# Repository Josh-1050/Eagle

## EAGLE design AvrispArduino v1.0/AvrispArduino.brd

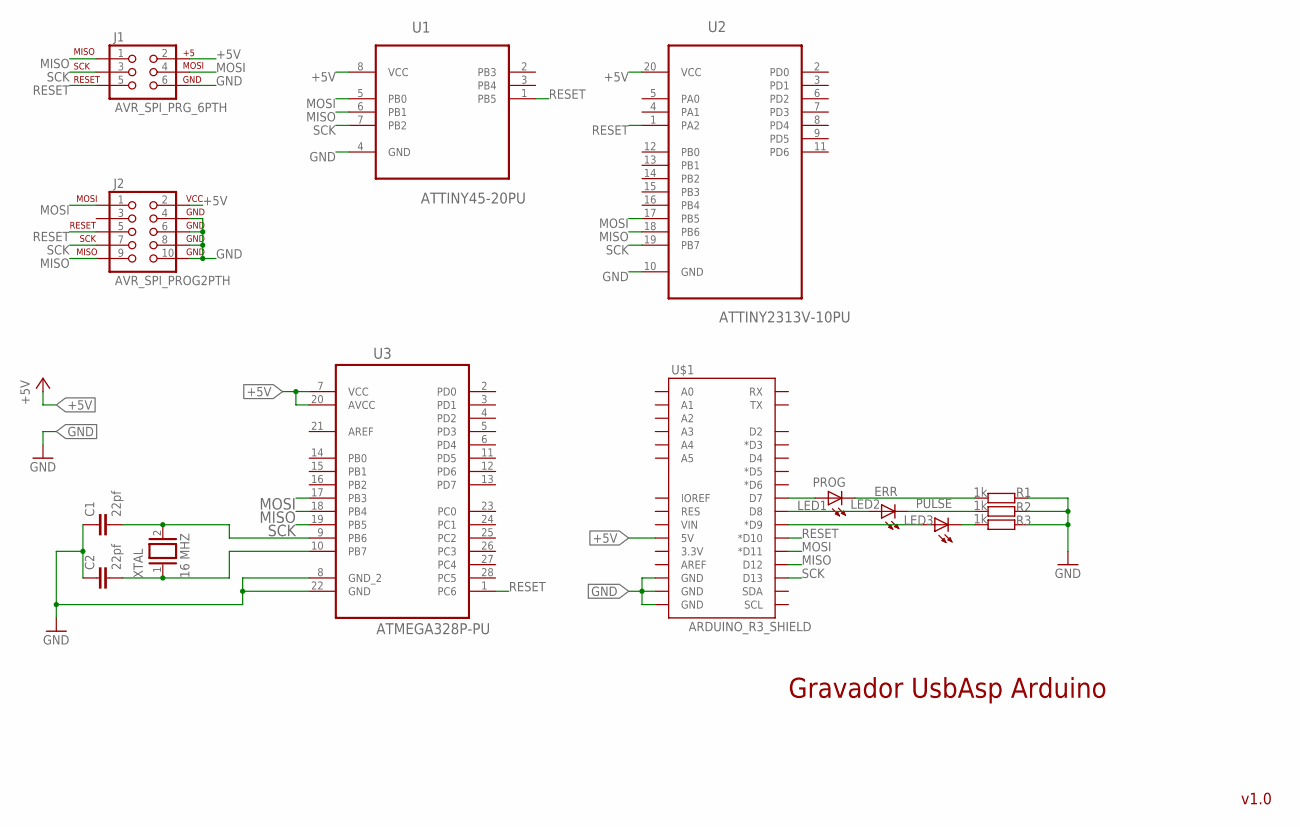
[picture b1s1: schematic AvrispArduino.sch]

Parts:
C1, C2: 22pf; C025-025X050
J1: AVR_SPI_PRG_6PTH; 2X3
J2: AVR_SPI_PROG2PTH; AVR_ICSP
LED1: PROG; LED3MM
LED2: ERR; LED3MM
LED3: PULSE; LED3MM
R1, R2, R3: 1k; 0207/10
U1: ATTINY45-20PU; DIP254P762X533-8
U2: ATTINY2313V-10PU; DIP254P762X533-20
U3: ATMEGA328P-PU; DIP254P762X457-28
U$1: ARDUINO_R3_SHIELD; UNO_R3_SHIELD
XTAL: 16 MHZ; QS

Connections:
+5V: J1.2, J2.2 (VCC), U1.8 (VCC), U2.20 (VCC), U3.7 (VCC), U3.20 (AVCC), U$1.5V
GND: C1.1, C2.1, J1.6, J2.4 (GND), J2.6 (GND), J2.8 (GND), J2.10 (GND), R1.2, R2.2, R3.2, U1.4 (GND), U2.10 (GND), U3.8 (GND_2), U3.22 (GND), U$1.GND@0 (GND), U$1.GND@1 (GND), U$1.GND@2 (GND)
MISO: J1.1, J2.9 (MISO), U1.6 (PB1), U2.18 (PB6), U3.18 (PB4), U$1.D12
MOSI: J1.4, J2.1 (MOSI), U1.5 (PB0), U2.17 (PB5), U3.17 (PB3), U$1.D11 (*D11)
unnamed: LED1.A, U$1.D7
unnamed: LED2.A, U$1.D8
unnamed: LED3.A, U$1.D9 (*D9)
unnamed: LED1.K (C), R1.1
unnamed: LED2.K (C), R2.1
unnamed: LED3.K (C), R3.1
unnamed: C1.2, U3.9 (PB6), XTAL.2
unnamed: C2.2, U3.10 (PB7), XTAL.1
RESET: J1.5, J2.5 (RESET), U1.1 (PB5), U2.1 (PA2), U3.1 (PC6), U$1.D10 (*D10)
SCK: J1.3, J2.7 (SCK), U1.7 (PB2), U2.19 (PB7), U3.19 (PB5), U$1.D13

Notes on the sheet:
Gravador UsbAsp Arduino
v1.0

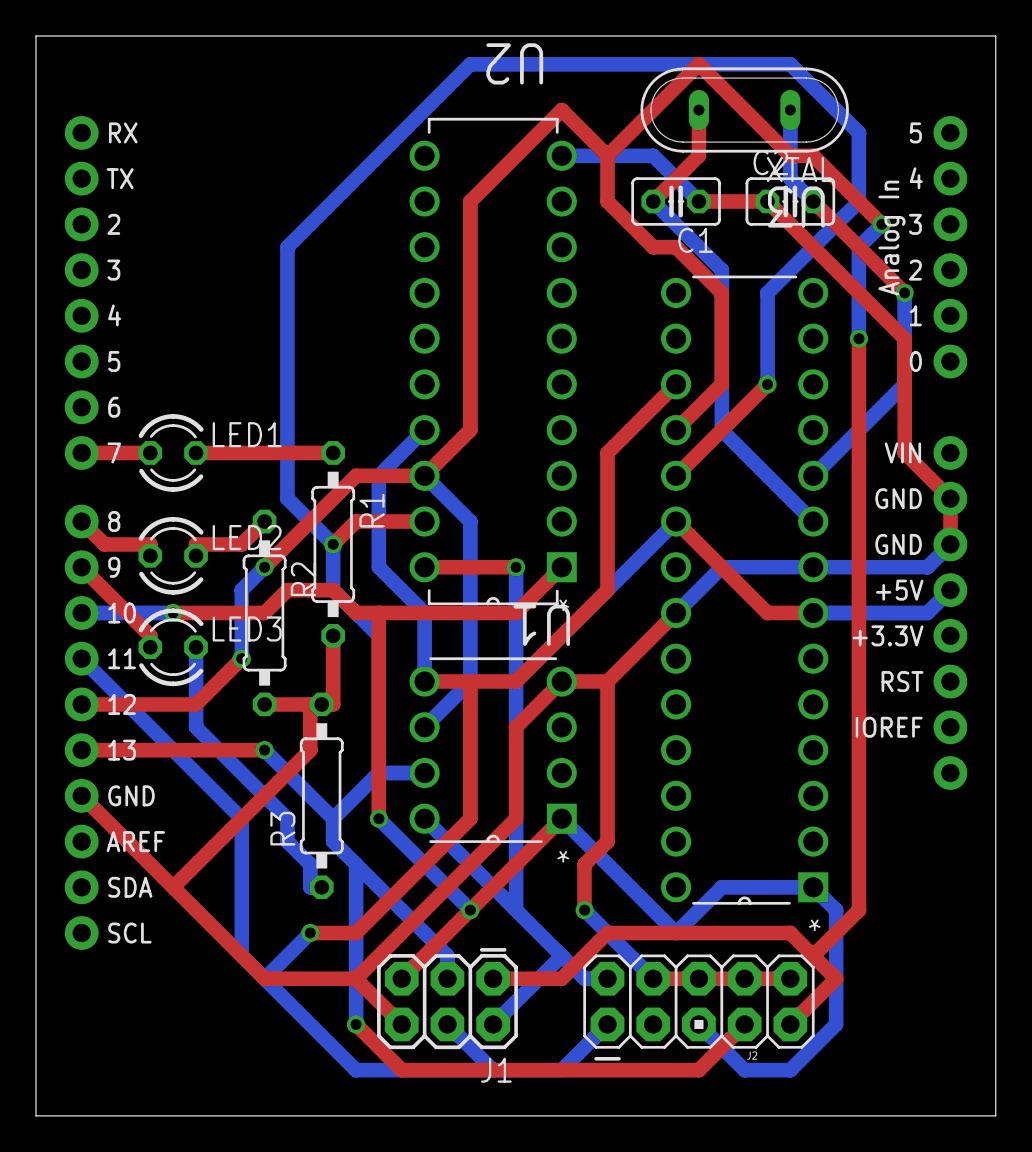
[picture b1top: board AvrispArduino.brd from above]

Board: 2 copper layers, 53.3 x 60.0 mm, 15 parts (0 on the bottom side), 14 nets.

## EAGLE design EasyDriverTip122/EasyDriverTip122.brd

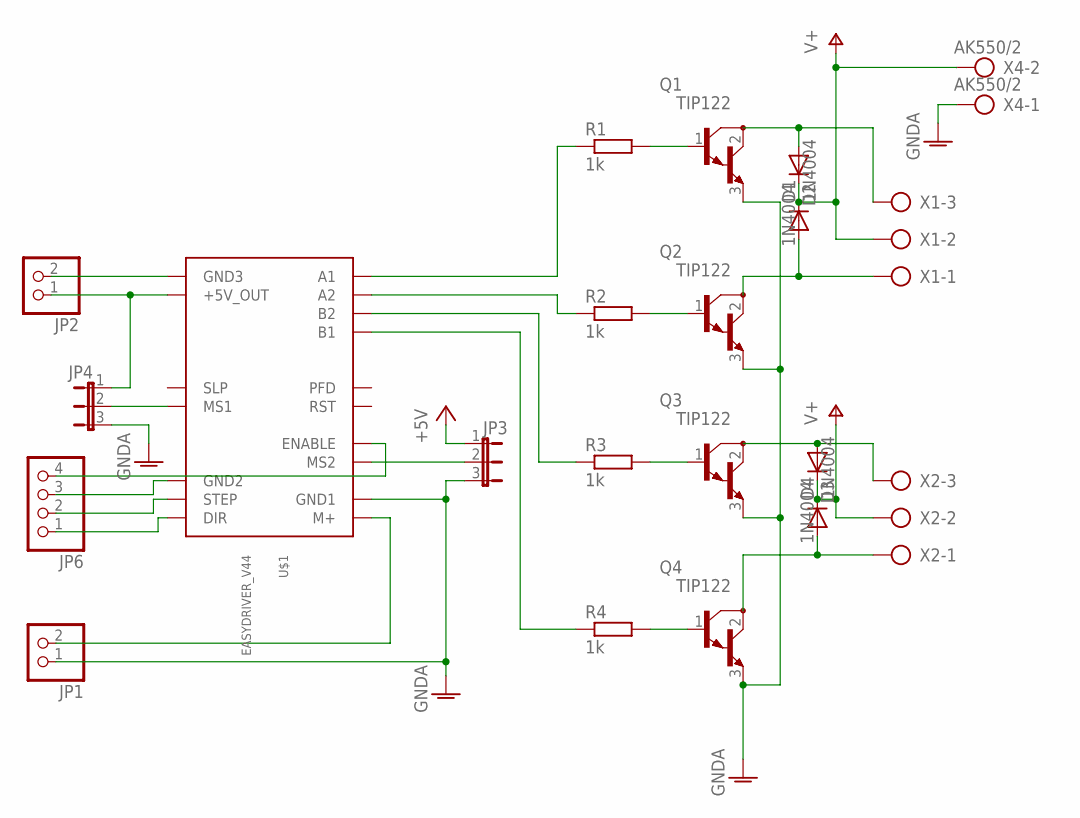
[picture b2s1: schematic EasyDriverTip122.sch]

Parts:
D1, D2, D3, D4: 1N4004; DO41-10
JP1, JP2: PINHD-1X2; 1X02
JP3, JP4: JP2E; JP2
JP6: PINHD-1X4; 1X04
Q1, Q2, Q3, Q4: TIP122; TO220V
R1, R2, R3, R4: 1k; 0204/7
U$1: EASYDRIVER_V44
X1, X2: AK500/3
X4: AK550/2

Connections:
+5V: JP2.1, JP3.1, JP4.1, U$1.P$11 (+5V_OUT)
GNDA: JP1.1, JP3.3, JP4.3, Q1.3 (E), Q2.3 (E), Q3.3 (E), Q4.3 (E), U$1.GND1, X4.1
unnamed: JP4.2, U$1.MS1
unnamed: JP3.2, U$1.MS2
unnamed: JP6.3, U$1.GND2
unnamed: JP6.2, U$1.STEP
unnamed: JP6.4, U$1.ENABLE
unnamed: JP1.2, U$1.M+
unnamed: JP2.2, U$1.GND3
unnamed: JP6.1, U$1.DIR
unnamed: Q1.1 (B), R1.2
unnamed: Q2.1 (B), R2.2
unnamed: Q3.1 (B), R3.2
unnamed: Q4.1 (B), R4.2
unnamed: R1.1, U$1.A1
unnamed: R2.1, U$1.A2
unnamed: R3.1, U$1.B2
unnamed: R4.1, U$1.B1
unnamed: D2.A, Q1.2 (C), X1.3
unnamed: D1.A, Q2.2 (C), X1.1
unnamed: D3.A, Q3.2 (C), X2.3
unnamed: D4.A, Q4.2 (C), X2.1
V+: D1.C, D2.C, D3.C, D4.C, X1.2, X2.2, X4.2

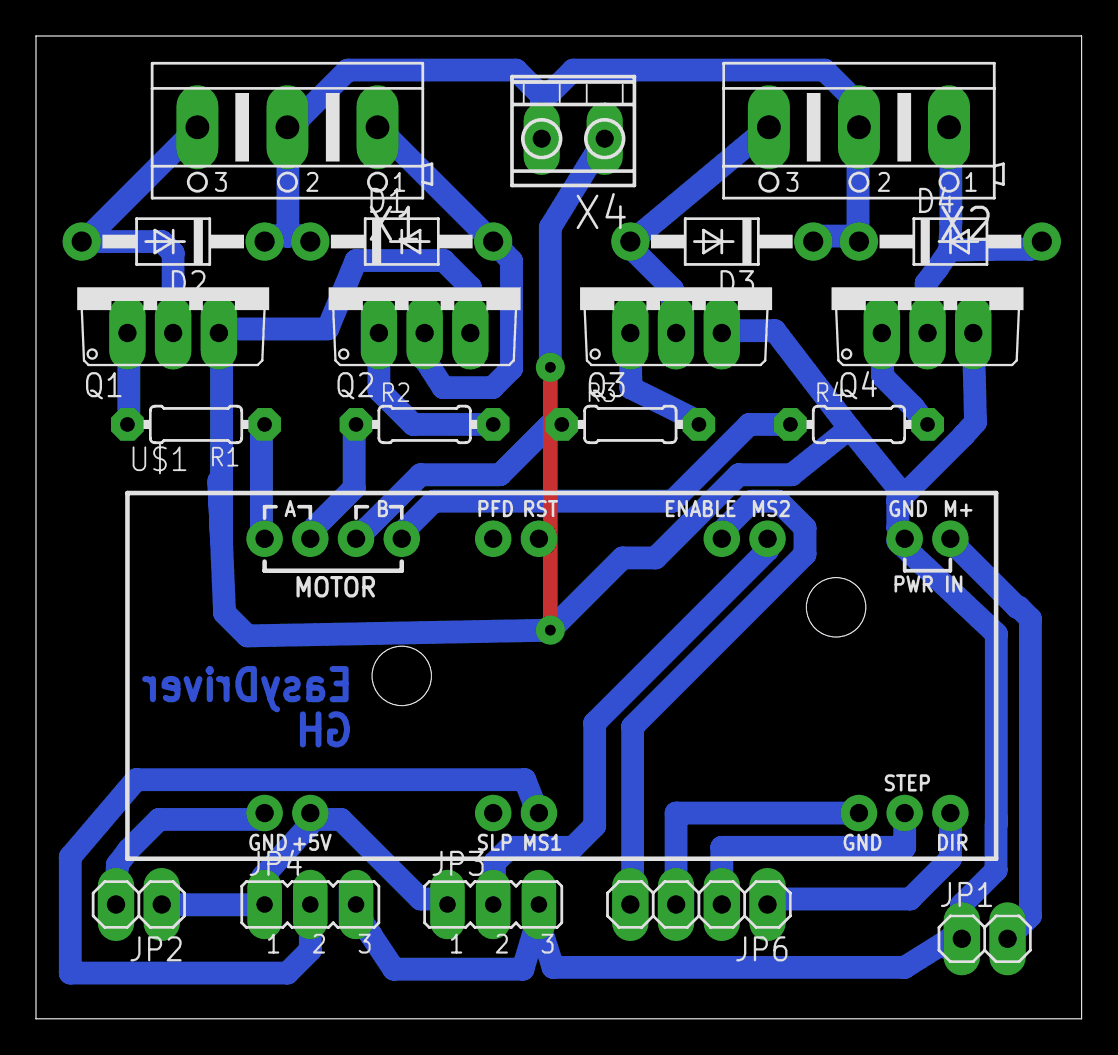
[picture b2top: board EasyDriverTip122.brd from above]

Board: 2 copper layers, 58.1 x 54.6 mm, 21 parts (0 on the bottom side), 23 nets.

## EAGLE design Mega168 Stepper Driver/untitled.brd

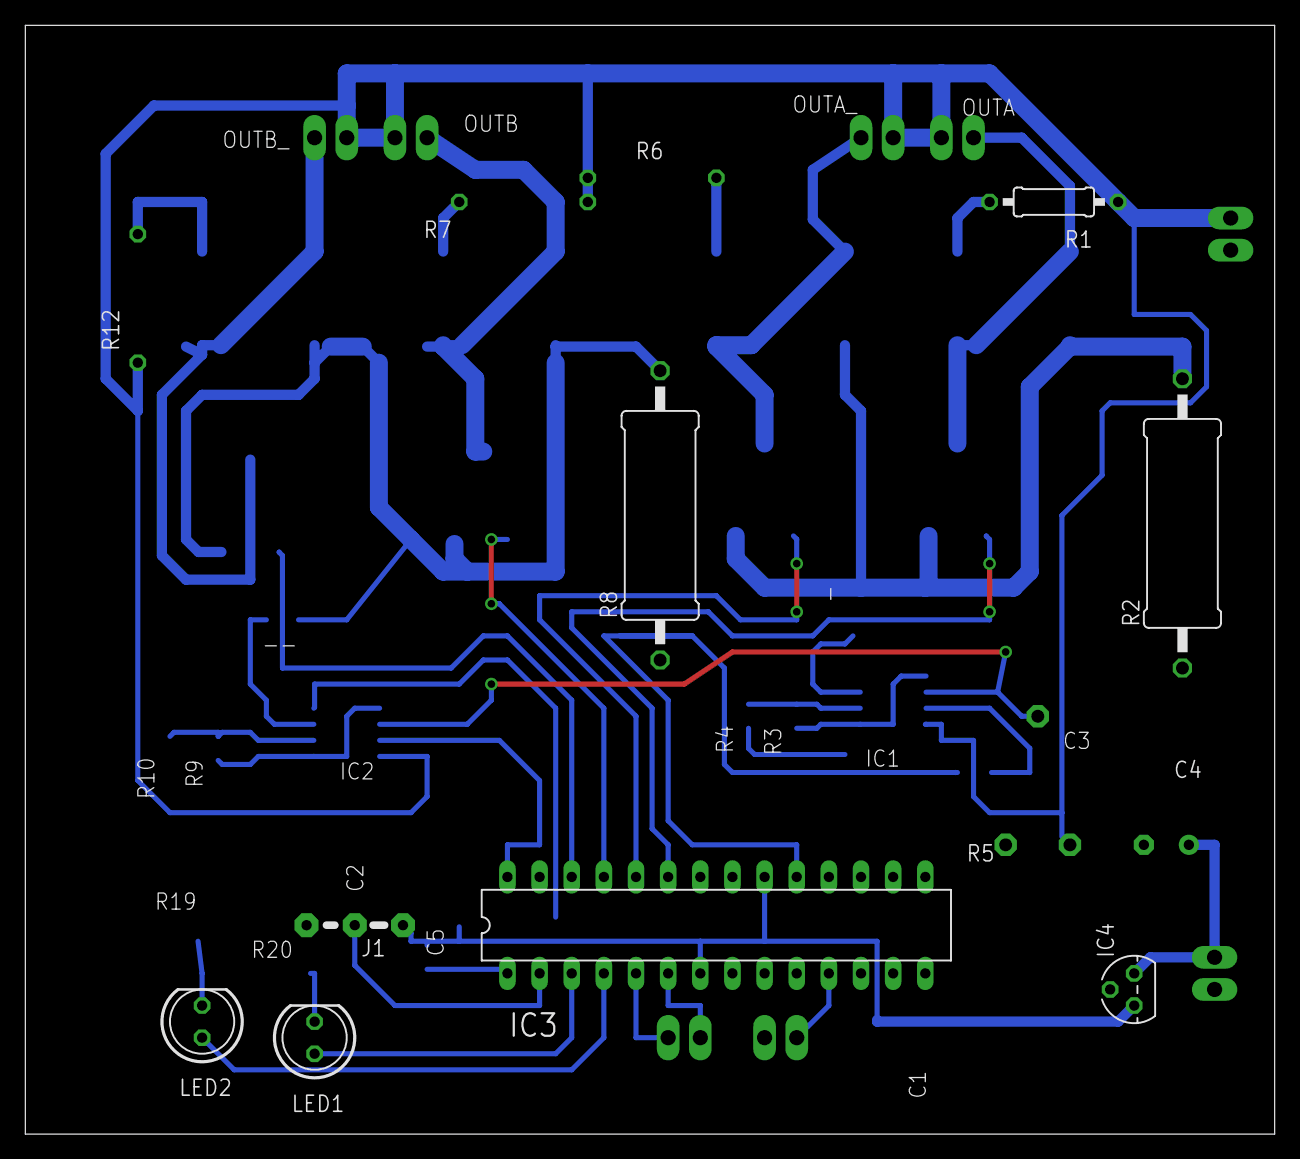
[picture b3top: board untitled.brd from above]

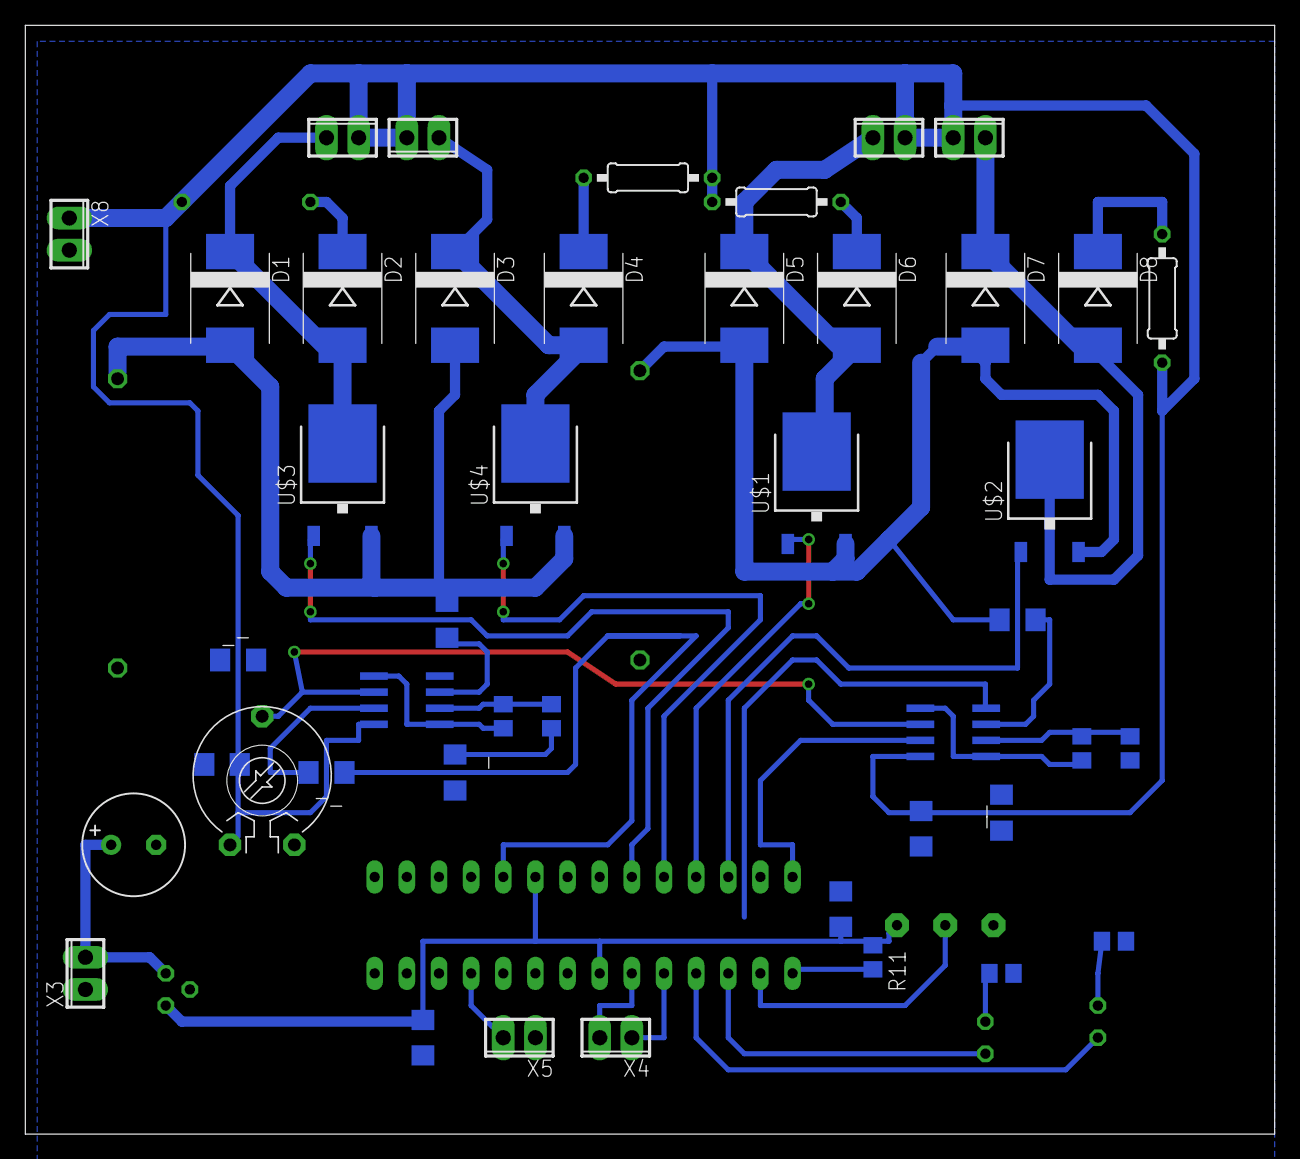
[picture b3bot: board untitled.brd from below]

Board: 2 copper layers, 98.7 x 87.6 mm, 52 parts (44 on the bottom side), 35 nets.

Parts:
-: R1206
--: R1206
-_: R1206
C1, C2, C3, C5: 0.1u; C1206
C4: 10u; E3,5-8
D1, D2, D3, D4, D5, D6, D7, D8: S3D; SMC
IC1, IC2: LM358D; SO08
IC3: MEGA48/88/168-PU; DIL28-3
IC4: 7805L; TO92
J1: 04C
LED1, LED2: LED5MM
OUTA: 2POL254
OUTA_: 2POL254
OUTB: 2POL254
OUTB_: 2POL254
R1, R6, R7, R12: 1k; 0207/10
R2, R8: 0.1; 0617/22
R3, R9, R11: 10k; R0805
R4, R10: 2.2k; R0805
R5: PT-10
R19, R20: 1K; R0805
U$1, U$2, U$3, U$4: NTD3055L104G; TO252
X3, X4, X5, X8: 2POL254
_: R1206
_-: R1206
__: R1206

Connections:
CTRLA: IC3.23, U$3.1
CTRLA_: IC3.24, U$4.1
CTRLB: IC3.25, U$1.1
CTRLB_: IC3.26, U$2.1
GND: C1.2, C2.1, C3.1, C4.-, C5.2, IC1.4, IC2.4, IC3.8, IC3.21, IC3.22, IC4.2, J1.3, R2.1, R4.2, R5.2, R8.1, R10.2, R19.2, R20.2, X3.1, X5.1, X8.2, _.1, _.2, _-.1, _-.2, __.1, __.2
unnamed: IC1.1, IC1.5, R3.1
unnamed: IC1.2, R3.2, R4.1
unnamed: -_.1, IC3.19
unnamed: IC2.7, IC3.28
unnamed: IC3.11, X5.2
unnamed: IC1.6, IC2.6, R5.3
unnamed: D1.C, D2.A, OUTA.1, U$3.3
unnamed: D2.C, R1.1
unnamed: C4.+, IC4.3, X3.2
unnamed: D3.C, D4.A, OUTA_.1, U$4.3
unnamed: D4.C, R6.1
unnamed: D1.A, D3.A, IC1.3, R2.2, U$3.2, U$4.2
unnamed: -_.2, IC1.7
unnamed: IC3.1, R11.2
unnamed: IC3.6, X4.2
unnamed: IC2.1, IC2.5, R9.1
unnamed: IC2.2, R9.2, R10.1
unnamed: LED2.K, R19.1
unnamed: C1.1, C5.1, IC3.7, IC3.20, IC4.1, J1.1, R11.1
unnamed: D5.C, D6.A, OUTB.1, U$1.3
unnamed: D6.C, R7.1
unnamed: D7.C, D8.A, OUTB_.2, U$2.3
unnamed: D8.C, R12.1
unnamed: D5.A, D7.A, IC2.3, R8.2, U$1.2, U$2.2
unnamed: LED1.K, R20.1
unnamed: IC3.5, X4.1
unnamed: IC3.4, LED2.A
unnamed: IC3.3, LED1.A
unnamed: IC3.2, J1.2
V+: C2.2, C3.2, IC1.8, IC2.8, OUTA.2, OUTA_.2, OUTB.2, OUTB_.1, R1.2, R5.1, R6.2, R7.2, R12.2, X8.1

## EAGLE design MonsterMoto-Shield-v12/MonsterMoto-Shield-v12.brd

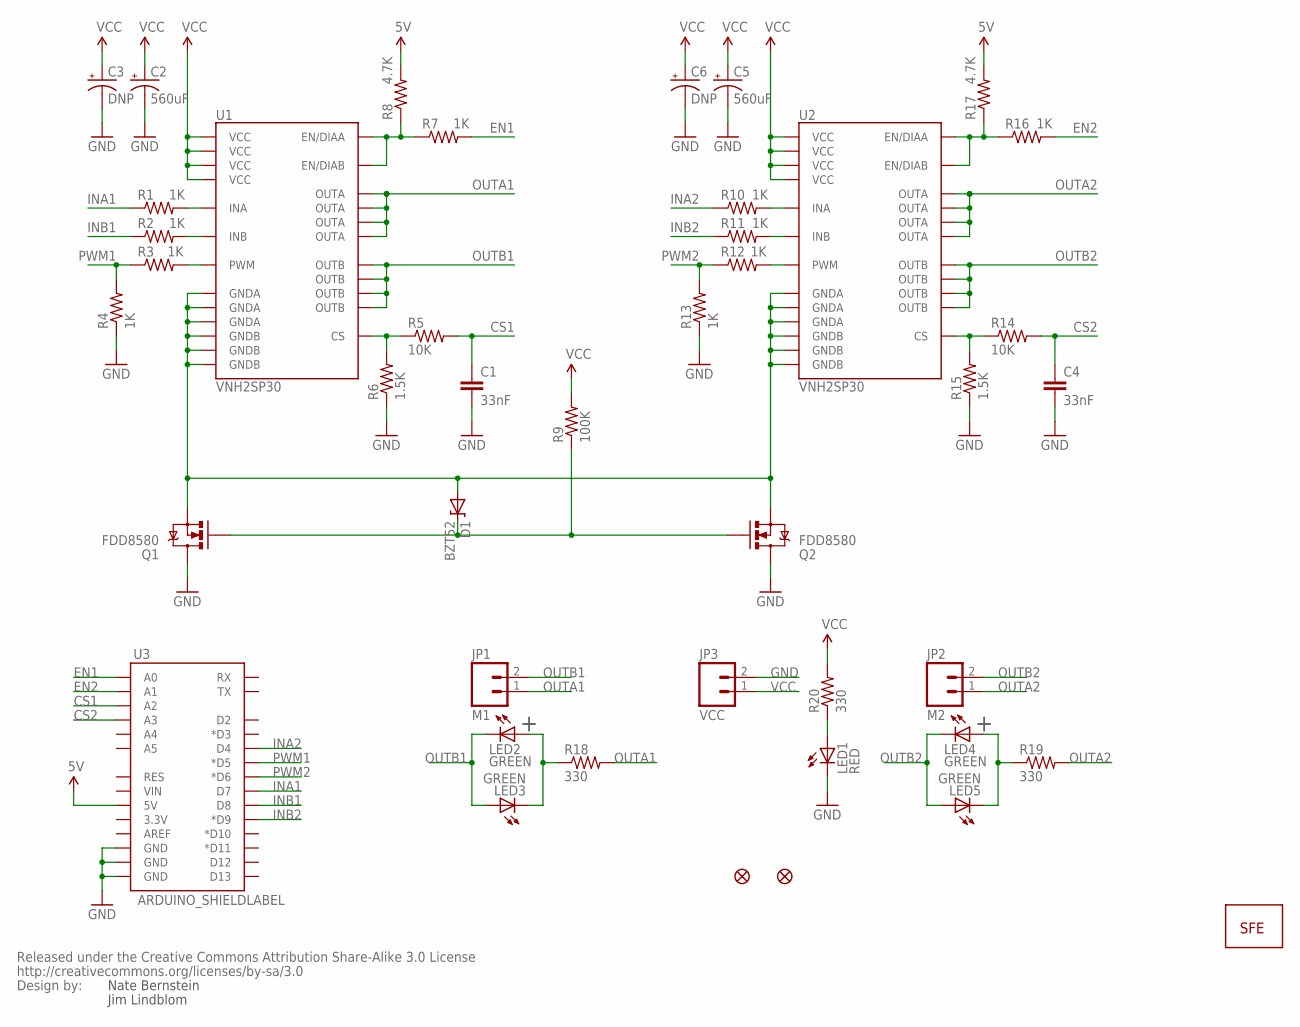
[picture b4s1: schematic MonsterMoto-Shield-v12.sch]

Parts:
C1, C4: 33nF; 0402-CAP
C2, C5: 560uF; PANASONIC_G
C3, C6: DNP; CPOL-RADIAL-1000UF-25V
D1: BZT52; SOD-323
JP1: M1; 1X02_XTRA_BIG
JP2: M2; 1X02_XTRA_BIG
JP3: VCC; 1X02_XTRA_BIG
JP4, JP6: FIDUCIAL1X2; FIDUCIAL-1X2
JP5: LOGO-SFENEW; SFE-NEW-WEBLOGO
LED1: RED; LED-0603
LED2, LED3, LED4, LED5: GREEN; LED-0603
Q1, Q2: FDD8580; DPAK
R1, R2, R3, R4, R7, R10, R11, R12, R13, R16: 1K; 0402-RES
R5, R14: 10K; 0402-RES
R6, R15: 1.5K; 0402-RES
R8, R17: 4.7K; 0402-RES
R9: 100K; 0402-RES
R18, R19, R20: 330; 0402-RES
U1, U2: VNH2SP30
U3: ARDUINO_SHIELDLABEL; DUEMILANOVE_SHIELD
U$6: CREATIVE_COMMONS

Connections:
5V: R8.2, R17.2, U3.5V
CS1: C1.1, R5.2, U3.A2
CS2: C4.1, R14.2, U3.A3
EN1: R7.2, U3.A0
EN2: R16.2, U3.A1
GND: C1.2, C2.-, C3.2 (-), C4.2, C5.-, C6.2 (-), JP3.2, LED1.C, Q1.4 (D), Q2.4 (D), R4.1, R6.1, R13.1, R15.1, U3.GND@0 (GND), U3.GND@1 (GND), U3.GND@2 (GND)
INA1: R1.1, U3.D7
INA2: R10.1, U3.D4
INB1: R2.1, U3.D8
INB2: R11.1, U3.D9 (*D9)
unnamed: R2.2, U1.11 (INB)
unnamed: R1.2, U1.5 (INA)
unnamed: R11.2, U2.11 (INB)
unnamed: R10.2, U2.5 (INA)
unnamed: R3.2, U1.8 (PWM)
unnamed: R12.2, U2.8 (PWM)
unnamed: R5.1, R6.2, U1.9 (CS)
unnamed: R14.1, R15.2, U2.9 (CS)
unnamed: R16.1, R17.1, U2.6 (EN/DIAA), U2.10 (EN/DIAB)
unnamed: D1.2 (A), Q1.3 (S), Q2.3 (S), U1.18 (GNDB), U1.19 (GNDB), U1.20 (GNDB), U1.26 (GNDA), U1.27 (GNDA), U1.28 (GNDA), U2.18 (GNDB), U2.19 (GNDB), U2.20 (GNDB), U2.26 (GNDA), U2.27 (GNDA), U2.28 (GNDA)
unnamed: R7.1, R8.1, U1.6 (EN/DIAA), U1.10 (EN/DIAB)
unnamed: D1.1 (C), Q1.1 (G), Q2.1 (G), R9.1
unnamed: LED2.A, LED3.C, R18.1
unnamed: LED4.A, LED5.C, R19.1
unnamed: LED1.A, R20.1
OUTA1: JP1.1, R18.2, U1.1 (OUTA), U1.25 (OUTA), U1.30 (OUTA), U1.SLUG3 (OUTA)
OUTA2: JP2.1, R19.2, U2.1 (OUTA), U2.25 (OUTA), U2.30 (OUTA), U2.SLUG3 (OUTA)
OUTB1: JP1.2, LED2.C, LED3.A, U1.15 (OUTB), U1.16 (OUTB), U1.21 (OUTB), U1.SLUG2 (OUTB)
OUTB2: JP2.2, LED4.C, LED5.A, U2.15 (OUTB), U2.16 (OUTB), U2.21 (OUTB), U2.SLUG2 (OUTB)
PWM1: R3.1, R4.2, U3.D5 (*D5)
PWM2: R12.1, R13.2, U3.D6 (*D6)
VCC: C2.+, C3.1 (+), C5.+, C6.1 (+), JP3.1, R9.2, R20.2, U1.3 (VCC), U1.13 (VCC), U1.23 (VCC), U1.SLUG1 (VCC), U2.3 (VCC), U2.13 (VCC), U2.23 (VCC), U2.SLUG1 (VCC)

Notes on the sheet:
Jim Lindblom
Nate Bernstein

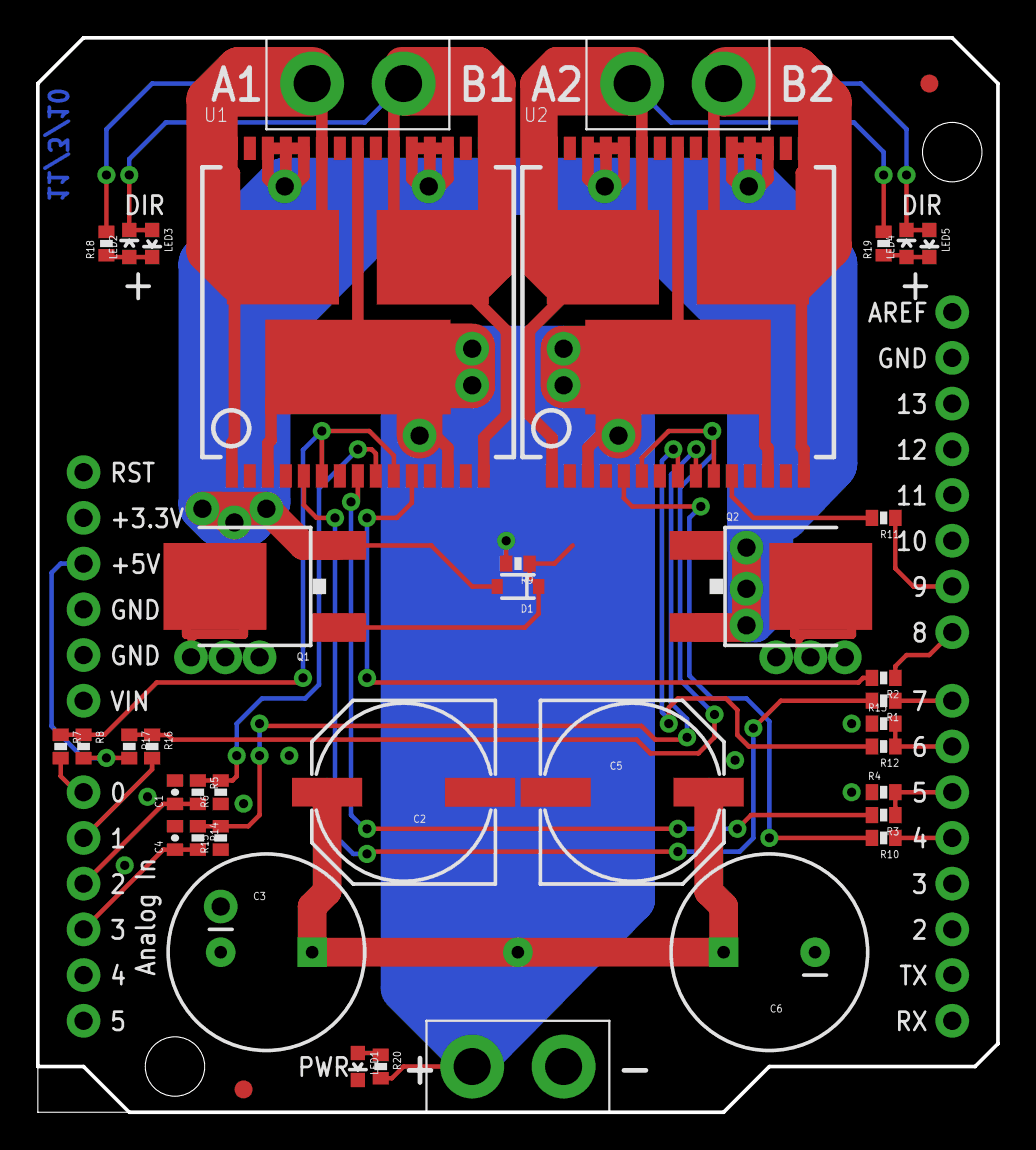
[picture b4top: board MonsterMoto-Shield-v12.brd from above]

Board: 2 copper layers, 53.3 x 59.7 mm, 44 parts (1 on the bottom side), 32 nets.

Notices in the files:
parts and their libraries:
SparkFun-Connectors: Licensing: Creative Commons ShareAlike 4.0 International - https://creativecommons.org/licenses/by-sa/4.0
SparkFun: Released under the Creative Commons Attribution Share-Alike 3.0 License
SparkFun: http://creativecommons.org/licenses/by-sa/3.0
